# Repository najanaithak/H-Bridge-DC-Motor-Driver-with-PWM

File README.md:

# H-Bridge-DC-Motor-Driver-with-PWM
H-Bridge DC Motor Driver using PWM with Proteus and KiCad.

# H-Bridge DC Motor Driver Using PWM Speed Control

## 📌 Overview

This project presents the design and simulation of an **H-Bridge DC Motor Driver** using **PWM (Pulse Width Modulation)** for precise speed control and bidirectional motor operation.

The complete workflow includes:

- STM32F103C8T6 (Blue Pill) Firmware
- Proteus Simulation
- KiCad PCB Design
- Gerber Manufacturing Files
- Documentation
- Experimental Results

---

## 🚀 Features

- PWM-based DC Motor Speed Control
- Forward & Reverse Motor Rotation
- H-Bridge MOSFET Driver
- STM32F103C8T6 Microcontroller
- KiCad PCB Design
- Proteus Simulation
- Gerber Files for PCB Fabrication
- Complete Documentation

---

## 🛠️ Software Used

| Software | Purpose |
|----------|---------|
| STM32CubeIDE | Firmware Development |
| KiCad | PCB Design |
| Proteus | Circuit Simulation |
| Microsoft Excel | Data Analysis |
| PowerPoint | Presentation |

---

## 📂 Repository Structure

```text
H-Bridge-DC-Motor-Driver-with-PWM
│
├── Report
├── Proteus
├── KiCad
├── Components
├── Results
├── Media
└── Docs
```

---

## ⚡ Hardware Components

- STM32F103C8T6 Blue Pill
- IRF9530 P-Channel MOSFET
- IRFZ44N N-Channel MOSFET
- 2N2222 NPN Transistor
- DC Motor
- 12V Power Supply
- Passive Components

---

## 📊 Project Outputs

- Proteus Simulation
- KiCad PCB Layout
- 3D PCB Model
- PWM Waveforms
- Performance Analysis
- Experimental Results

---

## 📸 Project Gallery

### Proteus Simulation

### PCB Layout

### 3D PCB

---

## 📄 Documentation

- Project Report
- Presentation
- Abstract
- References
- BOM
- Cost Analysis

---

## 📜 License

This project is released under the MIT License.

---

## 👨‍💻 Author

- Gnanesh Robbi
- Nimisha Manikandan
- Bharathraj Sarvanan
- Arshiya Nishanadar
- Rittam Das

---

⭐ If you found this repository useful, please consider giving it a Star.

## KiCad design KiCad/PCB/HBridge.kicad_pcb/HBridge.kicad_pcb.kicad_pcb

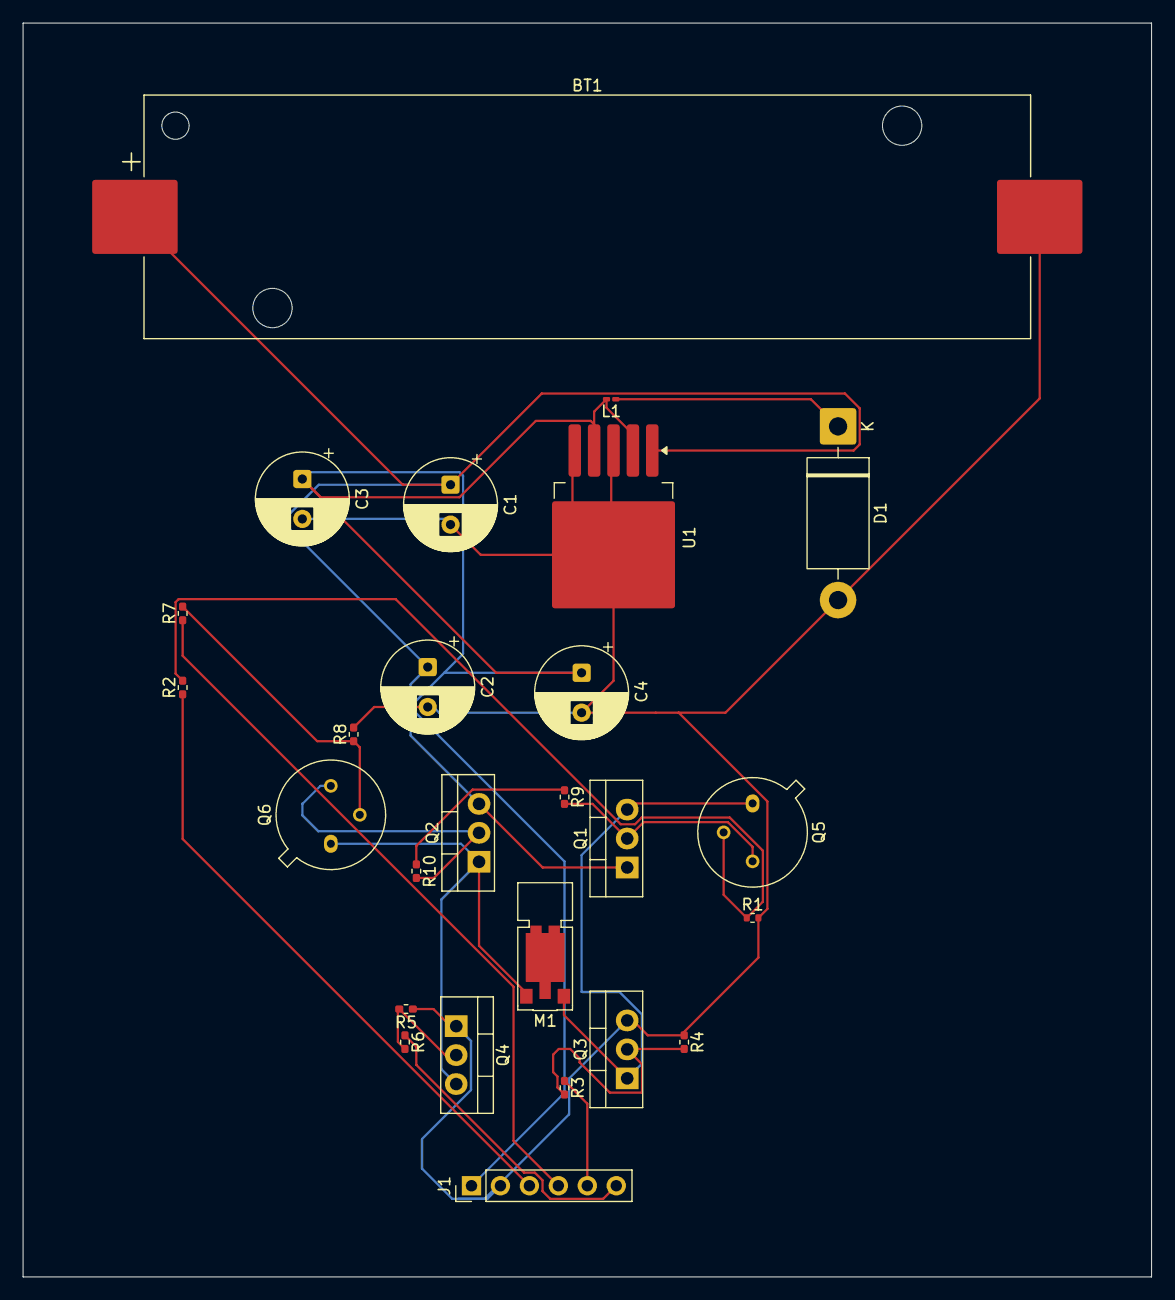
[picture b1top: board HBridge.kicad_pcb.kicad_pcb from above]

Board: 2 copper layers, 99.0 x 110.0 mm, 26 parts (0 on the bottom side), 17 nets.

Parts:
BT1: 12V; BatteryHolder_Keystone_1042_1x18650
C1: 220uF; CP_Radial_D8.0mm_P3.50mm
C2, C4: 100nF; CP_Radial_D8.0mm_P3.50mm
C3: 100uF; CP_Radial_D8.0mm_P3.50mm
D1: D_Schottky; D_DO-201AD_P15.24mm_Horizontal
J1: Conn_01x06; PinHeader_1x06_P2.54mm_Vertical
L1: 33uH; L_0201_0603Metric_Pad0.64x0.40mm_HandSolder
M1: Motor_DC; Vybronics_VZ30C1T8219732L
Q1, Q2: NMOS; TO-220-3_Vertical
Q3, Q4: PMOS; TO-220-3_Vertical
Q5, Q6: 2N2219; TO-39-3
R1: R; R_0402_1005Metric
R2, R3, R4, R5, R6, R7, R8, R9, R10: R; R_0402_1005Metric_Pad0.72x0.64mm_HandSolder
U1: LM2596S-3.3; TO-263-5_TabPin3

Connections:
GND: BT1.2 (-), C1.2, C2.2, C3.2, C4.2, D1.2 (A), J1.2, Q3.3 (S), Q4.1 (D), R1.2, R4.1, R5.1, R8.2, U1.3 (GND), U1.5 (~ON/OFF)
unnamed: BT1.1 (+), C1.1, C2.1, Q1.1 (D), Q2.3 (S), U1.1 (VIN)
unnamed: D1.1 (K), L1.1
unnamed: C3.1, C4.1, J1.1, L1.2, U1.2 (OUT), U1.4 (FB)
unnamed: J1.3, R2.1
unnamed: J1.4, R7.1
unnamed: J1.5, R3.1
unnamed: J1.6, R6.1
unnamed: M1.1 (+), Q1.3 (S), Q3.1 (D), Q5.1 (E)
unnamed: M1.2 (-), Q2.1 (D), Q4.3 (S), Q6.1 (E)
unnamed: Q1.2 (G), Q5.3 (C), R9.2
unnamed: Q2.2 (G), Q6.3 (C), R10.2
unnamed: Q3.2 (G), R3.2, R4.2
unnamed: Q4.2 (G), R5.2, R6.2
unnamed: Q5.2 (B), R1.1, R2.2
unnamed: Q6.2 (B), R7.2, R8.1
unnamed: R9.1, R10.1

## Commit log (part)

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2026-06-28 Create Report/.gitkeep
    Placeholder

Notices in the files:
README.md:
License: MIT
